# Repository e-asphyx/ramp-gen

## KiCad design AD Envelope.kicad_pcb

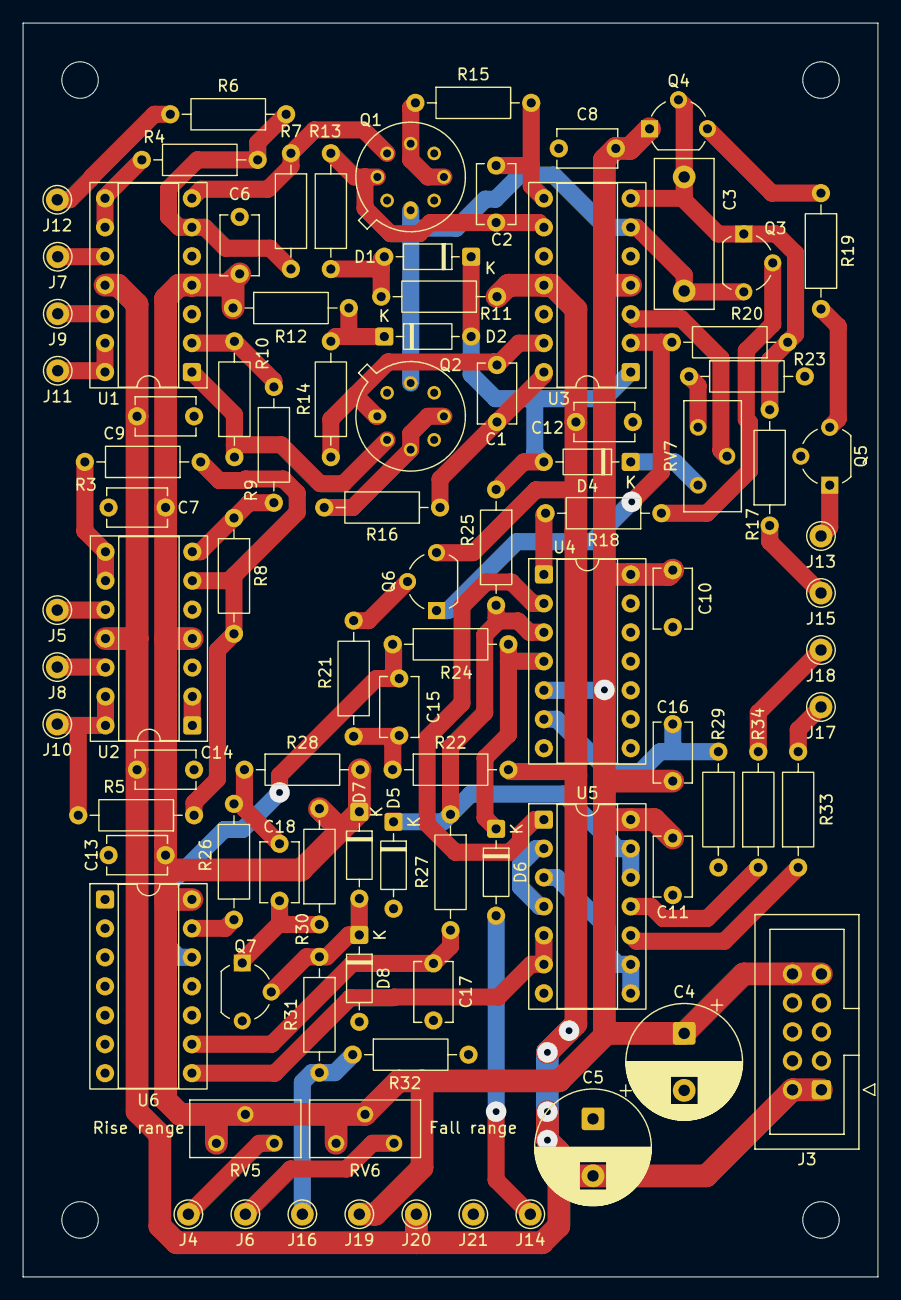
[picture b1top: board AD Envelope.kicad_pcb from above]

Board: 2 copper layers, 75.0 x 110.0 mm, 96 parts (0 on the bottom side), 63 nets.

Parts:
C1, C2, C15, C17: 0.1n; C_Disc_D5.1mm_W3.2mm_P5.00mm
C3: 47n; C_Rect_L13.0mm_W5.0mm_P10.00mm_FKS3_FKP3_MKS4
C4, C5: 100u; CP_Radial_D10.0mm_P5.00mm
C6, C7, C8, C9, C10, C11, C12, C13, C14: 0.1u; C_Disc_D5.1mm_W3.2mm_P5.00mm
C16: 10n; C_Disc_D5.1mm_W3.2mm_P5.00mm
C18: 1n; C_Disc_D5.1mm_W3.2mm_P5.00mm
D1, D2, D4, D5, D6, D7, D8: 1N4148; D_DO-35_SOD27_P7.62mm_Horizontal
H1, H2, H3, H4: MountingHole; MountingHole_3.2mm_M3
J3: Conn_02x05_Odd_Even; IDC-Header_2x05_P2.54mm_Vertical
J4, J5, J6, J7, J8, J9, J10, J11, J12, J13, J14, J15, J16, J17, J18, J19, J20, J21: Conn_01x01; Pin_D1.0mm_L10.0mm
Q1: AS395H; TO-5-8
Q2: AS394CH; TO-5-8
Q3, Q6, Q7: BS170; TO-92_Wide
Q4: BC546; TO-92_Wide
Q5: BC556; TO-92_Wide
R3, R4, R5, R6, R7, R8, R9, R10, R20, R22, R23, R25, R26, R29, R30, R31: 10k; R_Axial_DIN0207_L6.3mm_D2.5mm_P10.16mm_Horizontal
R11, R12: 2.2M; R_Axial_DIN0207_L6.3mm_D2.5mm_P10.16mm_Horizontal
R13, R14: 2.2k 1%; R_Axial_DIN0207_L6.3mm_D2.5mm_P10.16mm_Horizontal
R15, R16: 820; R_Axial_DIN0207_L6.3mm_D2.5mm_P10.16mm_Horizontal
R17, R33, R34: 1k; R_Axial_DIN0207_L6.3mm_D2.5mm_P10.16mm_Horizontal
R18, R21: 100; R_Axial_DIN0207_L6.3mm_D2.5mm_P10.16mm_Horizontal
R19: 4.7k; R_Axial_DIN0207_L6.3mm_D2.5mm_P10.16mm_Horizontal
R24: 33k; R_Axial_DIN0207_L6.3mm_D2.5mm_P10.16mm_Horizontal
R27: 22k; R_Axial_DIN0207_L6.3mm_D2.5mm_P10.16mm_Horizontal
R28: 47k; R_Axial_DIN0207_L6.3mm_D2.5mm_P10.16mm_Horizontal
R32: 100k; R_Axial_DIN0207_L6.3mm_D2.5mm_P10.16mm_Horizontal
RV5, RV6, RV7: 50k; Potentiometer_Bourns_3296Y_Vertical
U1, U2, U3: TL074; DIP-14_W7.62mm_Socket
U4: 4013; DIP-14_W7.62mm_Socket
U5: 4011; DIP-14_W7.62mm_Socket
U6: 40106; DIP-14_W7.62mm_Socket

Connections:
/CLK: D5.1 (K), R25.2, R27.1, U4.3 (C), U5.12, U5.13
/CMP_OUT: D1.1 (K), D2.2 (A), D4.2 (A), R25.1, U3.1
/CYCLE_EN: D6.2 (A), J14.1 (Pin_1_1)
/F_CV: Q1.6 (B2), R7.1, U1.7
/F_CV_BUF: J11.1 (Pin_1_1), U1.13 (-), U1.14
/F_CV_SUM_IN: J12.1 (Pin_1_1), R6.2
/F_CV_WIPER: J9.1 (Pin_1_1), U1.12 (+)
/F_OUT: J18.1 (Pin_1_1), R34.2
/F_POT_IN: J6.1 (Pin_1_1), RV6.3
/F_WIPER: J7.1 (Pin_1_1), U1.10 (+)
/INT_OUT: C3.2, Q3.1 (D), Q4.2 (B), R17.2, R20.1, U3.7
/LED: J13.1 (Pin_1_1), Q5.1 (C)
/Q: R18.2, U4.1 (Q)
/RAMP_OUT: J15.1 (Pin_1_1), R17.1
/RESET: D6.1 (K), R24.2, U4.4 (R)
/R_CV: Q2.2 (B1), R10.1, U1.1
/R_CV_BUF: J10.1 (Pin_1_1), R5.2, U2.13 (-), U2.14
/R_CV_WIPER: J8.1 (Pin_1_1), U2.12 (+)
/R_OUT: J17.1 (Pin_1_1), R33.2
/R_POT_IN: J4.1 (Pin_1_1), RV5.3
/R_WIPER: J5.1 (Pin_1_1), U2.10 (+)
/TRIG_IN: J16.1 (Pin_1_1), R31.2, R32.1
/~Q: U4.2 (~Q), U5.1
GND: C4.2, C5.1, C6.2, C7.2, C8.2, C9.1, C10.2, C11.2, C12.1, C13.2, C14.1, C17.2, D5.2 (A), D8.2 (A), J3.3, J3.4, J3.5, J3.6, J3.7, J3.8, J21.1 (Pin_1_1), Q1.2 (B1), Q2.6 (B2), Q5.2 (B), Q7.3 (S), R23.2, R29.2, R32.2, U1.3 (+), U1.5 (+), U2.3 (+), U2.5 (+), U3.5 (+), U3.10 (+), U3.12 (+), U4.7 (VSS), U4.8 (S), U4.9 (D), U4.10 (R), U4.11 (C), U5.7 (VSS), U6.1, U6.3, U6.5, U6.7 (VSS), U6.11
unnamed: C1.2, R16.1, U3.14
unnamed: C2.2, R15.2, U3.8
unnamed: C15.1, R21.2, R22.1
unnamed: C15.2, R24.1, U6.12
unnamed: C17.1, R27.2, U6.9
unnamed: C18.1, R26.1, R28.1
unnamed: D1.2 (A), R11.2, R13.1
unnamed: D2.1 (K), R12.2, R14.2
unnamed: D4.1 (K), RV7.3
unnamed: D7.2 (A), D8.1 (K), Q7.2 (G), R31.1
unnamed: C3.1, Q1.1 (C1), Q2.7 (C2), Q3.3 (S), U3.6 (-)
unnamed: Q1.3 (E1), Q1.5 (E2), R15.1
unnamed: C2.1, Q1.7 (C2), R13.2, U3.9 (-)
unnamed: C1.1, Q2.1 (C1), R14.1, U3.13 (-)
unnamed: Q2.3 (E1), Q2.5 (E2), R16.2
unnamed: Q3.2 (G), R18.1
unnamed: Q4.3 (E), R19.1
unnamed: Q5.3 (E), R19.2
unnamed: Q6.1 (D), R20.2, U3.2 (-)
unnamed: Q6.2 (G), R21.1
unnamed: C18.2, Q7.1 (D), R30.1
unnamed: R8.1, R9.2, U2.7
unnamed: R23.1, RV7.1
unnamed: R26.2, U6.13
unnamed: R33.1, U5.10
unnamed: R34.1, U5.11
unnamed: R9.1, R10.2, U1.2 (-)
unnamed: R4.1, R6.1, R7.2, U1.6 (-)
unnamed: R4.2, U1.8, U1.9 (-)
unnamed: U2.1, U2.2 (-)
unnamed: R3.1, R5.1, R8.2, U2.6 (-)
unnamed: R3.2, U2.8, U2.9 (-)
unnamed: RV7.2, U3.3 (+)
unnamed: C16.2, R29.1, U4.6 (S)
unnamed: U5.2, U5.4
unnamed: U5.3, U5.8, U5.9
unnamed: U5.5, U5.6, U6.8
VCC: C4.1, C6.1, C7.1, C8.1, C10.1, C11.1, C13.1, C16.1, D7.1 (K), J3.9, J3.10, J19.1 (Pin_1_1), Q4.1 (C), R12.1, R28.2, R30.2, RV5.1, RV5.2, RV6.1, RV6.2, U1.4 (V+), U2.4 (V+), U3.4 (V+), U4.5 (D), U4.14 (VDD), U5.14 (VDD), U6.14 (VDD)
VEE: C5.2, C9.2, C12.2, C14.2, J3.1, J3.2, J20.1 (Pin_1_1), Q6.3 (S), R11.1, R22.2, U1.11 (V-), U2.11 (V-), U3.11 (V-)
